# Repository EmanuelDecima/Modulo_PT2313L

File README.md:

# Módulo de Procesamiento de Audio PT2313L
Módulo estéreo de control de volumen, tono, balance y loudness basado en el integrado PT2313L. Diseñado para aplicaciones de audio Hi-Fi y sistemas de sonido personalizados.

## 🔧 Características
- Control digital de volumen, tono, balance y loudness mediante bus I²C.
- Entradas de audio estéreo con selección de canal.
- Alimentación simple de 9–12 V DC.
- Pines de control compatibles con microcontroladores (Arduino, STM32, ESP32, etc.).
- PCB de simple faz, tamaño compacto (100 mm × 50 mm).
- Boneras para alimentación y salidas de audio
- Conector JST para entradas de audio
- Conector de 4 pines para comunicación mediante bus I²C.

## 🖼️ Esquema y PCB

## ⚙️ Documentación técnica
El módulo está basado en el integrado **PT2313L**, un procesador de audio con control digital I²C.  
Las señales de audio ingresan a través de conectores JST y pasan por la etapa de selección y control del PT2313L antes de salir hacia el amplificador.  
Los niveles de volumen, balance y tono son programables por software.

## 🧰 Requisitos
- Controlador I²C (Arduino, STM32, ESP32, Raspberry Pi, etc.)
- Fuente de alimentación regulada 9–12 V DC
- Señal de audio de nivel de línea

## 🧠 Compatibilidad
Probado con:
- Arduino Nano / UNO
- STM32F103C8 ("Blue Pill")
- ESP32-WROOM

## 👤 Autor
Diseñado por Emanuel Décima  
📧 Contacto: emanueldecima3@gmail.com  
📅 Noviembre 2025

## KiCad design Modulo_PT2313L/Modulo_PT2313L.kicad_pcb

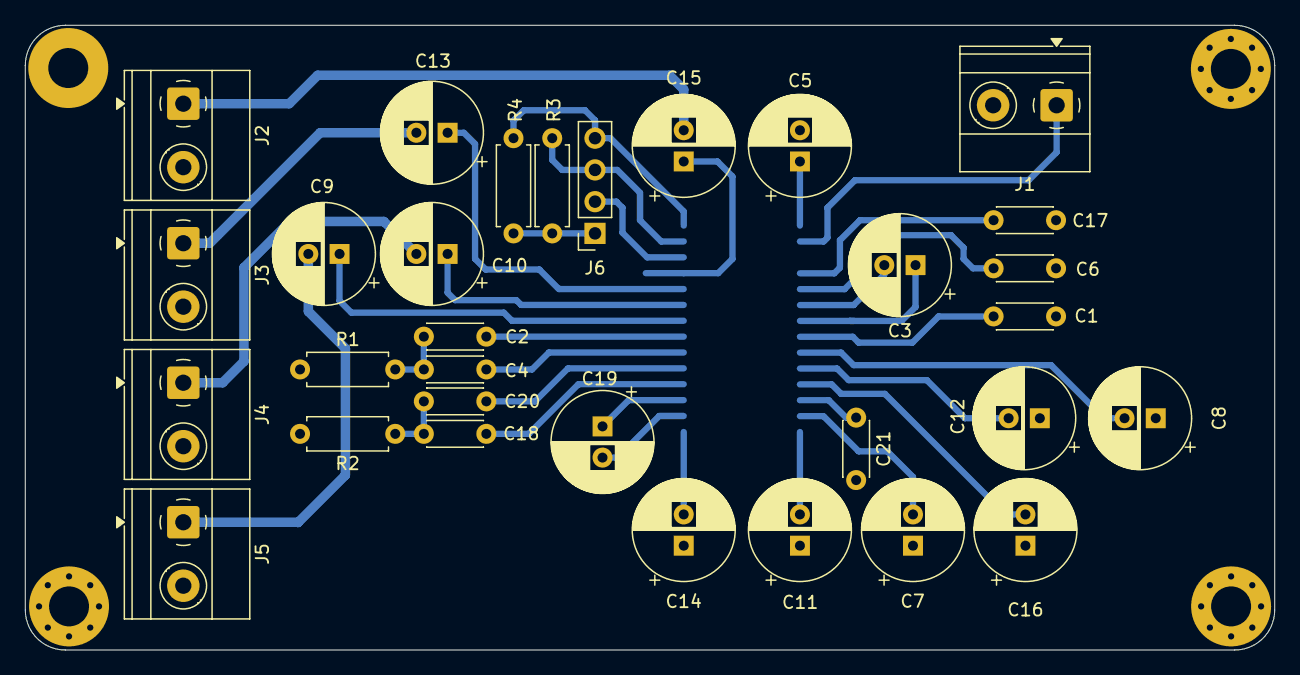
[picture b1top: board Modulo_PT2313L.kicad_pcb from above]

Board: 2 copper layers, 100.0 x 50.0 mm, 32 parts (1 on the bottom side), 35 nets.

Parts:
C1, C2, C4, C18, C20, C21: 100nF; C_Disc_D4.3mm_W1.9mm_P5.00mm
C3, C7, C8, C9, C10, C11, C12, C13, C14, C15, C16, C19: 2.2uF; CP_Radial_D8.0mm_P2.50mm
C5: 22uF; CP_Radial_D8.0mm_P2.50mm
C6, C17: 2,7nF; C_Disc_D4.3mm_W1.9mm_P5.00mm
J1: Power 9V; TerminalBlock_Phoenix_MKDS-1,5-2-5.08_1x02_P5.08mm_Horizont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
J2: LF_Amp; TerminalBlock_Phoenix_MKDS-1,5-2-5.08_1x02_P5.08mm_Horizont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
J3: RF_Amp; TerminalBlock_Phoenix_MKDS-1,5-2-5.08_1x02_P5.08mm_Horizont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
J4: LR_Amp; TerminalBlock_Phoenix_MKDS-1,5-2-5.08_1x02_P5.08mm_Horizont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
J5: RR_Amp; TerminalBlock_Phoenix_MKDS-1,5-2-5.08_1x02_P5.08mm_Horizont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
J6: Conn_01x04_Socket; PinSocket_1x04_P2.54mm_Vertical
R1, R2, R3, R4: 5K6; R_Axial_DIN0207_L6.3mm_D2.5mm_P7.62mm_Horizontal
U1: PT2313; SOIC-28W_7.5x17.9mm_P1.27mm

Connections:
+3V3: J6.1, R3.1, R4.1
GND: C1.2, C5.2, C6.2, C17.2, C21.2, J1.2, J2.2, J3.2, J4.2, J5.2, R1.2, R2.2, U1.3 (AGND)
GNDD: J6.2, U1.26 (DGND)
unnamed: C2.2, C4.2, R1.1
unnamed: C18.2, C20.2, R2.1
unnamed: C15.2, J2.1
unnamed: C13.2, J3.1
unnamed: C10.2, J4.1
unnamed: C9.2, J5.1
unnamed: J6.3, R3.2, U1.27 (DATA)
unnamed: J6.4, R4.2, U1.28 (CLK)
unnamed: C18.1, U1.18 (BIN_L)
unnamed: C4.1, U1.20 (BIN_R)
unnamed: C20.1, U1.19 (BOUT_L)
unnamed: C2.1, U1.21 (BOUT_R)
unnamed: C15.1, U1.25 (LFOUT)
unnamed: C14.2, U1.15 (LIN1)
unnamed: C11.2, U1.14 (LIN2)
unnamed: C7.2, U1.13 (LIN3)
unnamed: C19.2, U1.16 (LIN)
unnamed: C21.1, U1.12 (LOUD_L)
unnamed: C1.1, U1.8 (LOUD_R)
unnamed: C19.1, U1.17 (LOUT)
unnamed: C10.1, U1.23 (LROUT)
unnamed: C5.1, U1.1 (REF)
unnamed: C13.1, U1.24 (RFOUT)
unnamed: C16.2, U1.11 (RIN1)
unnamed: C12.2, U1.10 (RIN2)
unnamed: C8.2, U1.9 (RIN3)
unnamed: C3.2, U1.6 (RIN)
unnamed: C3.1, U1.7 (ROUT)
unnamed: C9.1, U1.22 (RROUT)
unnamed: C17.1, U1.4 (TREB_L)
unnamed: C6.1, U1.5 (TREB_R)
VDD: J1.1, U1.2 (VDD)

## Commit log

2025-11-06 primer commit
2025-11-07 PCB Diseñado
2025-11-07 Add README for PT2313L audio processing module
    Added detailed information about the PT2313L audio processing module, including features, documentation, requirements, compatibility, and author contact.
2025-11-07 agrego imagenes y esquematico
2025-11-07 Replace PCB images with front and back views
    Updated PCB design images in README.
2025-11-07 Change schematic image from PDF to PNG format
    Updated schematic image format from PDF to PNG.
2025-11-07 cambio imagen de esquematico a png
